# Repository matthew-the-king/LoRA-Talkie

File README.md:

# LoRA-Talkie

# FEATURES
Some features of the LoRA talkie are:<br>
1. Long Range Messaging
2. 5 keyboard switches for navigating the UI
3. Emergency switch that will sound an Alarm on the receiving end

# Parts
## Bill of Materials (BOM)

| Reference | Footprint | Quantity | Value | Links | Price |
|:---|:---|:---:|:---|:---|:---|
| B1 | BAT_BH-18650-PC_MPD | 1 | Holder | [Link](https://www.digikey.com/en/products/detail/mpd-memory-protection-devices/BH-18650-PC/3029216?s=N4IgTCBcDaIEIAkC0BGAHANgKwAYkAUBhEAXQF8g) | $3.35 |
| C1 | 0402 | 1 | 1uF | [Link](https://www.digikey.com/en/products/detail/samsung-electro-mechanics/CL05A105KO5NNNC/3886725) | $0.10 |
| C10, C11, C12, C13, C14, C15, C18, C19, C21, C3, C5, C9 | 0402 | 12 | 0.1uF | [Link](https://www.digikey.com/en/products/detail/yageo/CC0402KRX5R8BB104/5195106) | $0.56 |
| C16, C2, C20, C24, C4, C6, C7 | 0402 | 7 | 10uF | [Link](https://www.digikey.com/en/products/detail/murata-electronics/GRM155R60J106ME15D/5877401) |$0.95(buying 10 is cheaper than buying 7) |
| C17 | WCAP-PSHP_8X8.7_DXL_ | 1 | 470uF | [Link](https://www.digikey.com/en/products/detail/w%C3%BCrth-elektronik/875115252003/5147615) | $1.32 |
| C22, C23 | 0603 | 2 | 22uF | [Link](https://www.digikey.com/en/products/detail/holy-stone-enterprise-co-ltd/C0603B226M010T/16895513) | $0.68 |
| C8 | 0603 | 1 | 330nF | [Link](https://www.digikey.com/en/products/detail/tdk/CGA3E3X7R1H334K080AB/4931465) | $0.26 |
| D1 | D_SMA | 1 | 100V | [Link](https://www.digikey.com/en/products/detail/mcc-micro-commercial-components/SK310A-LTP/2642015) | $0.49 |
| FB1 | 0603 | 1 | 120R | [Link](https://www.digikey.com/en/products/detail/pulse-electronics/PE-0603PFB121ST/5050544) | $0.10 |
| J1 | SAMESKY_UJ20-C-H-G-SMT-1-P16-TR | 1 | USB_Charging | [Link](https://www.digikey.com/en/products/detail/same-sky-formerly-cui-devices/UJ20-C-H-G-SMT-P16-TR/24818595) | $0.65 |
| J2 | PinHeader_1x06_P2.54mm_Vertical | 1 | Conn_01x06_Pin | [Link](https://www.amazon.com/OCR-2-54mm-Breakaway-Connector-Arduino/dp/B0774VBJ3J/ref=sr_1_2_sspa?crid=3J6H8LMHZ3SS7&dib=eyJ2IjoiMSJ9.35ltPefTPqBOnQt_Ox_TI26xwO1SUs2D77_fY3-RewSFTh-Cg8mBGlhuQxJwY89Mr4AgBN51BE7EsK02txVfVMnuuAjss-PjZL7qeSK4j40VJrMjoEril4qtKCOSjhfoPAH9JvUulpll43v0f4zjy2FrXDKvMc4G_wxu7sPNflaKCRbgrA9vVlxch59x1EZD3Y7EnoJa7C-2_ka6BTX_5JUtUE_swCo9AXBNMqk3MVs.SY4UzEpKVAgJBn7IC6m1spKX7Eiw372FChIrKJbkStU&dib_tag=se&keywords=pin+headers&qid=1793638701&sprefix=pin+headers%2Caps%2C236&sr=8-2-spons&sp_csd=d2lkZ2V0TmFtZT1zcF9hdGY&psc=1) | $10 for a kit |
| J3 | CON_5051104091_MOL | 1 | 5051104091 | [Link](https://www.digikey.com/en/products/detail/molex/5051104091/5254662?s=N4IgTCBcDaIKwAY4EZkICwIJzJAXQF8g) | $2.25 |
| L1 | 1008 | 1 | 1.5uH | [Link](https://www.digikey.com/en/products/detail/murata-electronics/DFE252012P-1R5M-P2/5247259) | $0.22 |
| LS1 | CUI_CEM-1203_42_ | 1 | CEM-1203_42_ | [Link](https://www.digikey.com/en/products/detail/same-sky-formerly-cui-devices/CEM-1203-42/412412) | $1.04 |
| Q1 | SOT-23 | 1 | MMBT3904 | [Link](https://www.digikey.com/en/products/detail/mcc-micro-commercial-components/MMBT3904-TP/717280) | $0.11 |
| R1, R2 | 0402 | 2 | 5.1kΩ | [Link](https://www.digikey.com/en/products/detail/yageo/RC0402FR-075K1L/726624?s=N4IgTCBcDaIEoGEAMAWJYBicC0SDsArANICMAMiALoC%2BQA) | $0.20 |
| R10 | 0402 | 1 | 31.6kΩ | [Link](https://www.digikey.com/en/products/detail/panasonic-industry/ERA-2AEB3162X/2026187) | $0.11 |
| R11, R20, R21, R22, R3, R4, R5, R6, R7, R8 | 0402 | 10 | 10kΩ | [Link](https://www.digikey.com/en/products/detail/yageo/RC0402JR-0710KL/726418?s=N4IgTCBcDaIEoGEAMAWJYBScC0SDsAjEgNIAyIAugL5A) | $0.19 |
| R12 | 0402 | 1 | 100kΩ | [Link](https://www.digikey.com/en/products/detail/yageo/RC0402FR-07100KL/726526) | $0.10 |
| R13 | 0603 | 1 | 300Ω | [Link](https://www.digikey.com/en/products/detail/yageo/RC0603FR-07300RL/724356) | $0.10 |
| R14 | 0805 | 1 | 20Ω | [Link](https://www.digikey.com/en/products/detail/koa-speer-electronics-inc/RK73H2ATTD20R0F/10233961) | $0.10 |
| R15 | 2010 | 1 | 100Ω | [Link](https://www.digikey.com/en/products/detail/yageo/RT2010FKE07100RL/5945596) | $0.16 |
| R16, R17 | 0402 | 2 | 4.7kΩ | [Link](https://www.digikey.com/en/products/detail/yageo/RC0402JR-074K7L/726477) | $0.19(Cheaper to buy 10 than 2)|
| R18 | 2512 | 1 | 3.74Ω | [Link](https://www.digikey.com/en/products/detail/koa-speer-electronics-inc/RK73H3ATTE3R74F/10423886) | $0.34 |
| R19 | 0402 | 1 | 1kΩ | [Link](https://www.digikey.com/en/products/detail/panasonic-industry/ERJ-2RKF1001X/79729) | $0.10 |
| R9 | MSRSF3920P1L00D2P0 | 1 | 0.001Ω | [Link](https://www.digikey.com/en/products/detail/susumu/MSRSF3920P-1L00-D2P0/24396792) | $1.74 |
| S1 | SW_800SP9B6M6RE | 1 | Emergency_Button | [Link](https://www.digikey.com/en/products/detail/e-switch/800SP9B6M6RE/502079) | $3.34 |
| SW1, SW2, SW3, SW4, SW5 | SW-TH_MX1A-E1NW | 5 | MX1A-E1NW | [Link](https://www.digikey.com/en/products/detail/cherry-americas-llc/MX1A-C1NW/280855) | $6.25 |
| U1 | COMM-SMD_12P-L11.6-W11.0-P1.27_114993390 | 1 | WIO-SX1262_C9900174795 | [Link](https://www.digikey.com/en/products/detail/seeed-technology-co-ltd/114993390/25835823) | $5.95 |
| U2 | LQFP-48_7x7mm_P0.5mm | 1 | STM32L051C8Tx | [Link](https://www.digikey.com/en/products/detail/stmicroelectronics/STM32L010K4T6/9770447) | $1.96 |
| U3 | DSBGA8_YCK_TEX | 1 | BQ25188YBGR | [Link](https://www.digikey.com/en/products/detail/texas-instruments/BQ25188YBGR/25796454) | $2.55 |
| U4 | X2QFN08_1P5X1P5_TEX | 1 | BQ298215RUGR | [Link](https://www.digikey.com/en/products/detail/texas-instruments/BQ298218RUGR/24420965) | $0.76 |
| U5 | PSON50P145X100X60-6N | 1 | TPD4S012DRYR | [Link](https://www.digikey.com/en/products/detail/texas-instruments/TPD4S012DRYR/2037539) | $1.19 |
| U6 | IC_MCP16362T-E_NMX | 1 | MCP16362T-E_NMX | [Link](https://www.digikey.com/en/products/detail/microchip-technology/MCP16362T-E-NMXVAO/14291783) | $2.33 |
| U7 | TRANS_UT6J3_ROM | 1 | UT6K3TCR | [Link](https://www.digikey.com/en/products/detail/rohm-semiconductor/UT6K3TCR/6573277) | $1.23 |

Battery:[Link](https://www.digikey.com/en/products/detail/jauch-quartz/LIINR18650JD-26E-2-6AH/26408508),$10.02<br>
LCD Screen:[Link](https://www.digikey.com/en/products/detail/newhaven-display-intl/NHD-2-4-240320AF-CSXP/22204988), $13.94<br>
Use JLCPCB for the cheapest board cost; it is around $8 for 5 boards, plus $15 for shipping. 
# FIRMWARE

Not much here; I have not got the boards yet.

# PURPOSE OF PROJECT
The purpose of making the LoRA talkie was to deepen my understanding of LoRA devices, and in the Future I would really like to use a Non-module IC.
Also, I really wanted to make something that I could share with others, so a walkie-talkie seemed like an awesome choice.

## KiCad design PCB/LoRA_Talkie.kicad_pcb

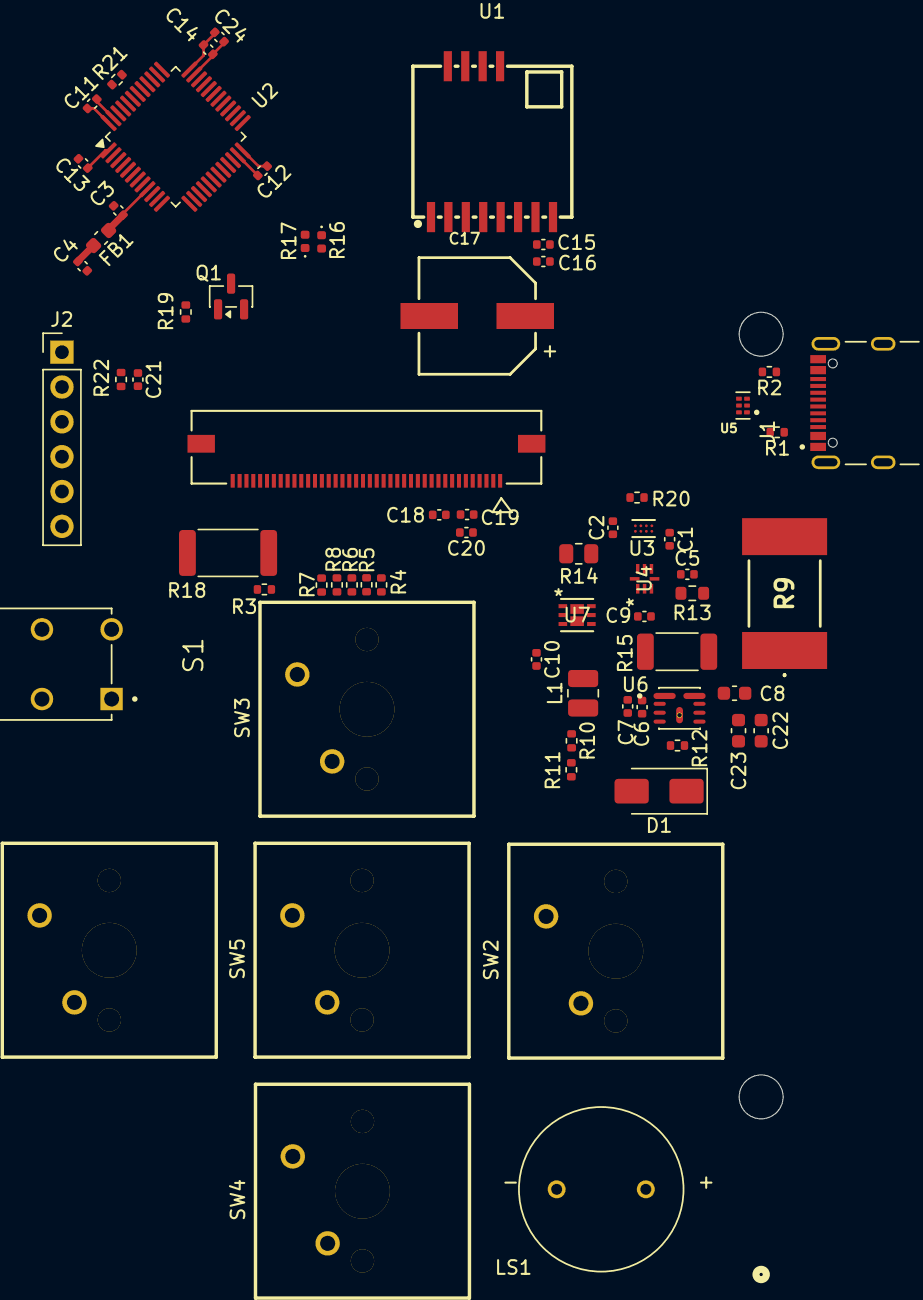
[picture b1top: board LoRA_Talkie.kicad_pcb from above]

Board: 2 copper layers, 68 parts (1 on the bottom side), 51 nets.

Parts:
B1: Holder; BAT_BH-18650-PC_MPD
C1: 1uF; C_0402_1005Metric
C2, C4, C6, C7, C16, C20, C24: 10uF; C_0402_1005Metric
C3, C5, C9, C10, C11, C12, C13, C14, C15, C18, C19, C21: 0.1uF; C_0402_1005Metric
C8: 330nF; C_0603_1608Metric
C17: 470uF; WCAP-PSHP_8X8.7_DXL_
C22, C23: 22uF; C_0603_1608Metric
D1: 100V; D_SMA
FB1: 120R; C_0603_1608Metric
J1: USB_Charging; SAMESKY_UJ20-C-H-G-SMT-1-P16-TR
J2: Conn_01x06_Pin; PinHeader_1x06_P2.54mm_Vertical
J3: 5051104091; CON_5051104091_MOL
L1: 1.5uH; L_1008_2520Metric
LS1: CEM-1203_42_; CUI_CEM-1203_42_
Q1: MMBT3904; SOT-23
R1, R2: 5.1kΩ; R_0402_1005Metric
R3, R4, R5, R6, R7, R8, R11, R20, R21, R22: 10kΩ; R_0402_1005Metric
R9: 0.001Ω; MSRSF3920P1L00D2P0
R10: 31.6kΩ; R_0402_1005Metric
R12: 100kΩ; R_0402_1005Metric
R13: 300Ω; R_0603_1608Metric
R14: 20Ω; R_0805_2012Metric
R15: 100Ω; R_2010_5025Metric
R16, R17: 4.7kΩ; LED_0402_1005Metric
R18: 3.74Ω; R_2512_6332Metric
R19: 1kΩ; R_0402_1005Metric
S1: Emergency_Button; SW_800SP9B6M6RE
SW1, SW2, SW3, SW4, SW5: MX1A-E1NW; SW-TH_MX1A-E1NW
U1: WIO-SX1262_C9900174795; COMM-SMD_12P-L11.6-W11.0-P1.27_114993390
U2: STM32L051C8Tx; LQFP-48_7x7mm_P0.5mm
U3: BQ25188YBGR; DSBGA8_YCK_TEX
U4: BQ298215RUGR; X2QFN08_1P5X1P5_TEX
U5: TPD4S012DRYR; PSON50P145X100X60-6N
U6: MCP16362T-E_NMX; IC_MCP16362T-E_NMX
U7: UT6K3TCR; TRANS_UT6J3_ROM

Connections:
+3.3V: C4.1, C11.1, C12.1, C13.1, C14.1, C15.1, C16.1, C17.1, C18.1, C19.2, C20.2, C22.1, C23.1, C24.1, FB1.2, J2.5, J3.7 (VDD), J3.8 (VDDI), J3.31 (IM0), J3.33 (IM2), L1.2, LS1.P, R3.1, R4.1, R5.1, R6.1, R7.1, R8.1, R10.1, R12.2, R16.2, R17.1, R18.1, R22.1, U1.8 (VCC), U2.1 (VDD), U2.24 (VDD), U2.36 (VDDIO2), U2.48 (VDD), U6.6 (BD)
/BAT: R13.1, R14.2, U7.1 (S1)
/BOOST: C8.1, U6.7 (BOOST)
/BOOT0: J2.1, R21.1, U2.44 (BOOT0)
/BUSY: U1.11 (BUSY), U2.20 (PB2)
/B_Gate: Q1.1 (B), R19.2
/CHG: U4.8 (CHG), U7.2 (G1)
/CTR: R15.1, U4.5 (CTR)
/DIO1: U1.12 (DIO1), U2.11 (PA1)
/DOWN_BUTTON: R7.2, SW4.1, U2.31 (PA10)
/DSG: U4.7 (DSG), U7.5 (G2)
/Emergency_Switch: R3.2, S1.1, U2.12 (PA2)
/LCD_MISO: J3.6 (SD0), U2.27 (PB14)
/LCD_MOSI: J3.9 (SDA), U2.28 (PB15)
/LCD_SCK: J3.11 (DCX), U2.21 (PB10)
/LEDA: J3.38 (LEDA), R18.2
/LEFT_BUTTON: R4.2, SW1.1, U2.33 (PA12)
/MIDDLE_BUTTON: R8.2, SW5.1, U2.32 (PA11)
/MISO_RF: U1.2 (MISO), U2.16 (PA6)
/MOSI_RF: U1.3 (MOSI), U2.17 (PA7)
/NRST: C21.2, J2.2, R22.2, U2.7 (NRST)
/NSS_RF: U1.6 (NSS), U2.14 (PA4)
/PACK+: U3.C2 (BAT), U4.6 (PACK), U7.4 (S2)
/PG: R12.1, U6.4 (PG)
/RF_NRST: U1.5 (NRST), U2.13 (PA3)
/RIGHT_BOTTOM: R5.2, SW2.1, U2.30 (PA9)
/SCL: R17.2, U2.42 (PB6), U3.B1 (SCL)
/SDA: R16.1, U2.43 (PB7), U3.C1 (SDA)
/SPI_SCK_RF: U1.4 (SCK), U2.15 (PA5)
/SYS: C2.1, C6.1, C7.1, U3.B2 (SYS), U6.1 (VIN), U6.2 (EN)
/SYS_SWCLK: J2.3, U2.37 (PA14)
/SYS_SWDIO: J2.4, U2.34 (PA13)
/TE: J3.40 (TE), U2.25 (PB12)
/TS/MR: R20.1, U3.D1 (TS/MR)
/UP_BOTTOM: R6.2, SW3.1, U2.29 (PA8)
/VBUS: C1.1, J1.A4_B9 (VBUS), J1.B4_A9 (VBUS__1), U3.A2 (IN), U5.6 (VBUS)
/VDD: C5.1, R13.2, U4.2 (VDD)
/VDDA: C3.1, FB1.1, U2.9 (VDDA)
/VSS: R9.1, U4.3 (VSS)
GND: C1.2, C2.2, C3.2, C4.2, C5.2, C6.2, C7.2, C9.2, C10.2, C11.2, C12.2, C13.2, C14.2, C15.2, C16.2, C17.2, C18.2, C19.1, C20.1, C21.1, C22.2, C23.2, C24.2, D1.2 (A), J1.A1_B12 (GND), J1.B1_A12 (GND__1), J1.SH1 (SHIELD), J1.SH2 (SHIELD__1), J1.SH3 (SHIELD__2), J1.SH4 (SHIELD__3), J2.6, J3.1 (GND), J3.32 (IM1), J3.34 (LEDK1), J3.35 (LEDK2), J3.36 (LEDK3), J3.37 (LEDK4), J3.39 (GND), J3.P1, J3.P2, Q1.2 (E), R1.2, R2.2, R9.2, R11.2, R20.2, R21.2, S1.3, SW1.2, SW2.2, SW3.2, SW4.2, SW5.2, U1.7 (GND), U1.10 (GND), U2.8 (VSSA), U2.23 (VSS), U2.35 (VSS), U2.47 (VSS), U3.D2 (GND), U4.4 (CS), U5.4 (GND), U6.5 (GND), U6.9 (EP)
unnamed: C10.1, R15.2
unnamed: C8.2, D1.1 (K), L1.1, U6.8 (SW)
unnamed: J1.A5 (CC1), R1.1
unnamed: J1.B5 (CC2), R2.1
unnamed: J1.A7 (DN1), J1.B7 (DN2), U5.2 (D-)
unnamed: J1.A6 (DP1), J1.B6 (DP2), U5.1 (D+)
unnamed: J3.12 (WRX), J3.13 (RDX), J3.14 (DB0), J3.15 (DB1), J3.16 (DB2), J3.17 (DB3), J3.18 (DB4), J3.19 (DB5), J3.20 (DB6), J3.21 (DB7), J3.22 (DB8), J3.23 (DB9), J3.24 (DB10), J3.25 (DB11), J3.26 (DB12), J3.27 (DB13), J3.28 (DB14), J3.29 (DB15)
unnamed: LS1.N, Q1.3 (C)
unnamed: R19.1, U2.38 (PA15)
unnamed: C9.1, R14.1, U4.1 (BAT)
unnamed: R10.2, R11.1, U6.3 (FB)

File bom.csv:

Designator,Footprint,Quantity,Value,LCSC Part #
B1,BAT_BH-18650-PC_MPD,1,Holder,
C1,0402,1,1uF,
"C10, C11, C12, C13, C14, C15, C18, C19, C21, C3, C5, C9",0402,12,0.1uF,
"C16, C2, C20, C24, C4, C6, C7",0402,7,10uF,
C17,WCAP-PSHP_8X8.7_DXL_,1,470uF,
"C22, C23",0603,2,22uF,
C8,0603,1,330nF,
D1,D_SMA,1,100V,
FB1,0603,1,120R,
J1,SAMESKY_UJ20-C-H-G-SMT-1-P16-TR,1,USB_Charging,
J2,PinHeader_1x06_P2.54mm_Vertical,1,Conn_01x06_Pin,
J3,CON_5051104091_MOL,1,5051104091,
L1,1008,1,1.5uH,
LS1,CUI_CEM-1203_42_,1,CEM-1203_42_,
Q1,SOT-23,1,MMBT3904,
"R1, R2",0402,2,5.1kΩ,
R10,0402,1,31.6kΩ,
"R11, R20, R21, R22, R3, R4, R5, R6, R7, R8",0402,10,10kΩ,
R12,0402,1,100kΩ,
R13,0603,1,300Ω,
R14,0805,1,20Ω,
R15,2010,1,100Ω,
"R16, R17",0402,2,4.7kΩ,
R18,2512,1,3.74Ω,
R19,0402,1,1kΩ,
R9,MSRSF3920P1L00D2P0,1,0.001Ω,
S1,SW_800SP9B6M6RE,1,Emergency_Button,
"SW1, SW2, SW3, SW4, SW5",SW-TH_MX1A-E1NW,5,MX1A-E1NW,C5120587
TP1,TestPoint_Pad_D2.0mm,1,TestPoint,
U1,COMM-SMD_12P-L11.6-W11.0-P1.27_114993390,1,WIO-SX1262_C9900174795,C9900174795
U2,LQFP-48_7x7mm_P0.5mm,1,STM32L051C8Tx,
U3,DSBGA8_YCK_TEX,1,BQ25188YBGR,
U4,X2QFN08_1P5X1P5_TEX,1,BQ298215RUGR,
U5,PSON50P145X100X60-6N,1,TPD4S012DRYR,
U6,IC_MCP16362T-E_NMX,1,MCP16362T-E_NMX,
U7,TRANS_UT6J3_ROM,1,UT6K3TCR,

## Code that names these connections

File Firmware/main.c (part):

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    /* USER CODE END WHILE */
	  GPIO_PinState Up_Button = HAL_GPIO_ReadPin(GPIOA, GPIO_PIN_8);
	  GPIO_PinState Right_Button = HAL_GPIO_ReadPin(GPIOA, GPIO_PIN_9);
	  GPIO_PinState Down_Button = HAL_GPIO_ReadPin(GPIOA, GPIO_PIN_10);
	  GPIO_PinState Middle_Button = HAL_GPIO_ReadPin(GPIOA, GPIO_PIN_11);
	  GPIO_PinState Left_button = HAL_GPIO_ReadPin(GPIOA, GPIO_PIN_12);

	  if (Up_Button == GPIO_PIN_SET)
	  {
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
	  }

	  if (Down_Button == GPIO_PIN_SET)
	  {

	  }

	  if (Middle_Button == GPIO_PIN_SET)
	  {
		  if (Cursor_Position[0] == 1 && Cursor_Position[1] = 0) // X=1, Y=0 is the position of send button
		  {
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		  }
	  }

	  if (Left_button == GPIO_PIN_SET)
	  {

	  }
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  /*Configure GPIO pin Output Level */
  HAL_GPIO_WritePin(GPIOA, GPIO_PIN_1|GPIO_PIN_3, GPIO_PIN_RESET);

  /*Configure GPIO pins : PA1 PA3 */
  GPIO_InitStruct.Pin = GPIO_PIN_1|GPIO_PIN_3;
  GPIO_InitStruct.Mode = GPIO_MODE_OUTPUT_PP;
  GPIO_InitStruct.Pull = GPIO_NOPULL;
  GPIO_InitStruct.Speed = GPIO_SPEED_FREQ_LOW;
  HAL_GPIO_Init(GPIOA, &GPIO_InitStruct);

  /*Configure GPIO pins : PA2 PA8 PA9 PA10
                           PA11 PA12 */
  GPIO_InitStruct.Pin = GPIO_PIN_2|GPIO_PIN_8|GPIO_PIN_9|GPIO_PIN_10
                          |GPIO_PIN_11|GPIO_PIN_12;
  GPIO_InitStruct.Mode = GPIO_MODE_INPUT;
  GPIO_InitStruct.Pull = GPIO_NOPULL;
  HAL_GPIO_Init(GPIOA, &GPIO_InitStruct);

  /*Configure GPIO pins : PB2 PB12 PB13 */
  GPIO_InitStruct.Pin = GPIO_PIN_2|GPIO_PIN_12|GPIO_PIN_13;
  GPIO_InitStruct.Mode = GPIO_MODE_INPUT;
  GPIO_InitStruct.Pull = GPIO_NOPULL;
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

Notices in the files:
Firmware/main.c:
Copyright (c) 2026 STMicroelectronics.
All rights reserved.
This software is licensed under terms that can be found in the LICENSE file
